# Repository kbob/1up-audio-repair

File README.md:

# Repair a 1UP's headphone jack.

This is a prototype of the
[1Bitsy-1UP](https://github.com/1Bitsy/1bitsy-1up)'s new audio output
section.  It is being implemented as a daughter card, but if it works,
it will be integrated into a future version of the 1Up

## Objectives

The new audio section will have these features.

 * Stereo headphone out or mono speaker out.

* Automatic switching between speaker and headphone when 'phones are
   plugged in.

* Thumbwheel for volume control.

* The volume wheel will directly control audio gain, but will also be
  readable by software.

* Headphone presence will directly control audio signal routing, but
  will also be readable by software. Software will produce stereo
  signal when the headphones are active and mono signal when the
  speaker is active.

* The amplifier's mute function will be controllable by software.

* The amplifier's shutdown (low power) function will be controllable
* by software.

## The Design

The audio output will be built around the PAM8019 amplifier from
Diodes Incorporated.  Headphone outputs will be routed to a 3.5mm
headphone jack.  Speaker outputs will be routed to a terminal block
for an off-board speaker.

The board will be configurable to take power either from the 1Bitsy's
+3v3 rail or from a separate power connection.

## Considerations

This is speculation based on the PAM8019 datasheet.

The 8019's digital input pins, MUTE and ~SD, are 3V compatible.  When
the 8019 is at 5V, a 3.3V GPIO will control those inputs.

The HP/~SPK input is not 3V compatible when the 8019 is at 5V.  The
HP/~SPK input will be generated directly from the headphone tip
switch.  In 5V operation, the 3V GPIO signal will be generated from a
voltage divider.  In 3V operation, the GPIO signal can be connected
directly to the tip switch.  (The GPIO pin happens to be an analog
input, so we could also leave the voltage divider in and read an
analog value instead of digital.)

The 8019's Volume input needs to have a range of 0 to +5V to give the
maximum attenuation of -60dB.  But the STM32's analog input can't
exceed 3.3v.  So a voltage divider is called for.  The problem is that
the Volume voltage already comes from a 50K potentiometer, which is a
voltage divider.  Adding another will make the volume control
nonlinear.

The 8019 has a circuit to detect low power and fade out the audio when
it happens.  It is supposed to suppress pops on power down.  It will
require experimentation to find the best resistor values for that.

The 8019 has a "non clip power limit" circuit.  The voltage at the PL
pin determines the maximum power the amp will deliver.  I will put in
a header to attach an external potentiometer to test various values of
PL with whatever speakers we decide to use.

## Interface

The board will connect directly to the 1Bitsy at the following
pins.  The pin arrangement will match the 1Bitsy's arrangement
so the boards can be stacked.

* +3V3
* GND
* PA0 for headphone tip sense
* PA1 for volume sense
* PA2 for Mute control
* PA3 for ~Shutdown control
* PA4/DAC1
* PA5/DAC2

A solder jumper will connect the amplifier VDD to the 1Bitsy's 3v3
supply.

There will be headers to attach external potentiometers or resistor
networks to dial in the correct values for the UVP and PL pins.

## Misc.

Here is a Maxim app note describing a headphone sense circuit.  Thanks
to James Hagerman for finding it and to an anonymous Maxim engineer
for writing it.

https://www.maximintegrated.com/en/app-notes/index.mvp/id/4607

## Errata

v0.2 holes are too small for the headphone jack.

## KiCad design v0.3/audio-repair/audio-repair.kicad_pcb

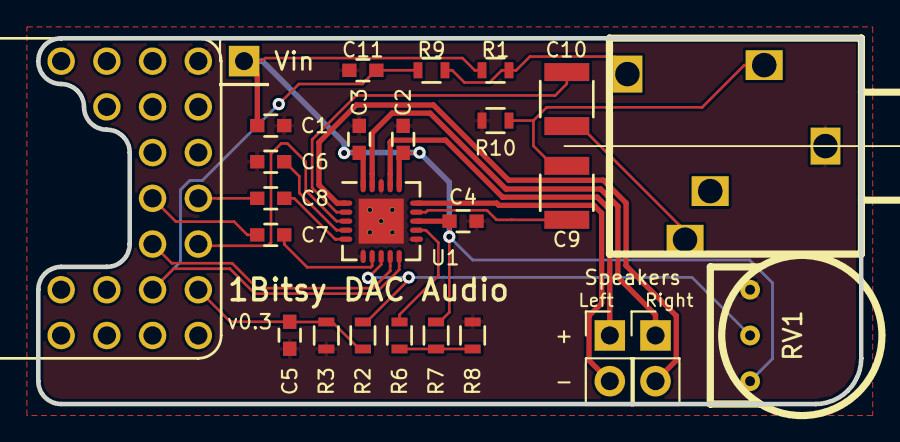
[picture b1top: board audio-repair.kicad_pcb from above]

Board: 2 copper layers, 45.7 x 20.3 mm, 26 parts (0 on the bottom side), 23 nets.

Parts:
C1: 10µF; C_0603
C2, C3, C4, C11: 100nF; C_0603
C5: 10nF; C_0603
C6: 1µF; C_0603
C7, C8: 220nF; C_0603
C9, C10: 220µF; C_1210
J1: Vin; Pin_Header_Straight_1x01_Pitch2.54mm
J2: Switchcraft_35RAPC4BHN3
J4: Left; Pin_Header_Straight_1x02_Pitch2.54mm
J6: Right; Pin_Header_Straight_1x02_Pitch2.54mm
R1: 100K; R_0603
R2: 680K; R_0603
R3: 1M; R_0603
R6, R8: 33K; R_0603
R7: 18K; R_0603
R9: 51K; R_0603
R10: 10K; R_0603
RV1: 50K; Potentiometer_Bourns_3352T
U1: PAM8019KGR; QFN-20-1EP_4x4mm_Pitch0.5mm
U2: 1bitsy-basic-stubby; 1bitsy-stub

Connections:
/DAC_L: C7.2, U2.35
/DAC_R: C8.2, U2.36
/MUTE: U1.9, U2.33
/TIP_SW: C11.1, R9.2, U1.10, U2.31
/VOL_ADC: C5.1, R2.2, R3.1, U2.32
/~SHUTDOWN: U1.3, U2.34
GND: C1.2, C2.2, C3.2, C4.2, C5.2, C6.2, C11.2, J2.1, R3.2, R8.2, R10.1, RV1.1, U1.6, U1.11, U1.18, U1.21, U2.16
unnamed: C6.1, U1.4
unnamed: C7.1, U1.7
unnamed: C8.1, U1.5
unnamed: C9.1, U1.14
unnamed: C9.2, J2.5, R10.2
unnamed: C10.1, U1.2
unnamed: C10.2, J2.2
unnamed: J2.4, R1.2, R9.1
unnamed: J4.1, U1.17
unnamed: J4.2, U1.15
unnamed: J6.1, U1.19
unnamed: J6.2, U1.1
unnamed: R2.1, RV1.2, U1.8
unnamed: R6.1, R7.2, R8.1
unnamed: R6.2, U1.12
VDD: C1.1, C2.1, C3.1, C4.1, J1.1, R1.1, R7.1, RV1.3, U1.13, U1.16, U1.20

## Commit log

2017-10-22 Describe what this board should be and do.
2017-10-22 Add headphone sense pins to interface, mention 0603 passives.
2017-10-24 Add board schematic.
2017-10-24 Check in latecomers.
2017-10-26 Write up discussion of amplifier chips.
2017-10-27 Start over with a completely different audio design.
2017-10-27 Draw most of the schematic.
2017-10-28 Design headphone/speaker switch control.
2017-10-30 Create footprints, rough-place components on board.
2017-10-30 Align 1bitsy pins to 0.1" grid.
2017-10-30 Align through-hole components to 0.1" grid.
2017-10-30 Route all traces except ground pours.
2017-10-31 Pour grounds, clean up silkscreen.
2017-10-31 Re-genericize the labels on library footprints.
2017-10-31 Moved all files to a v0.1 folder.
2017-10-31 Change pads in QFN footprint per @esden's suggestions.
2017-11-01 Layout v0.2 board (50x50mm).
2017-11-01 Add mounting holes; tweak stuff.
2017-11-01 Change 3.3v jumper from solder jumper to pin header.
2017-11-01 Change Gerbil plot settings.
2017-11-18 Create board stuffing guide.
2018-02-27 Start some comments in README about the next version (v0.3?)
2018-03-02 start v0.3 board revision.
2018-03-03 Create v0.3 schematic with lessons learned from v0.2.
2018-03-04 lay out v0.3 board.
